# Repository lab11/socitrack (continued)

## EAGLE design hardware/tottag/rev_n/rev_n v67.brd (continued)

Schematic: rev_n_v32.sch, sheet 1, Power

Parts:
C7, C8: 22pF; 0201_CAP; MPN GRM0335C1H220FA01D
C9, C10: 470pF; 0402_CAP; MPN GRM1555C1H471JA01J; DIGIKEY 490-6242-1-ND
C15, C16: 10nF; 0402_CAP; MPN GRM155R71H103KA88J; DIGIKEY 490-6351-2-ND
C17, C18, C19: 22nF; 0402_CAP; MPN GRM155R71E223JA61D; DIGIKEY 490-10699-2-ND
C20, C21: 22nF; 0402_CAP; MPN CC0402ZRY5V8BB223; DIGIKEY 311-3823-1-ND
C27, C28, C29, C30: 0.1uF; 0402_CAP; MPN GRM155R71C104KA88J; DIGIKEY 490-6328-1-ND
C38, C39: 0.47uF; 0402_CAP; MPN GRT155R61E474ME01D; DIGIKEY 490-12270-1-ND
C40, C41, C42: 1uF; 0402_CAP; MPN GRM155R70J105KA12J
C45, C46, C47, C48: 4.7uF; 0603_CAP; MPN C1608X7S1A475K080AC
C53, C56, C57: 10uF; 0603_CAP; MPN CM105X5R106M25AT; DIGIKEY 1253-CM105X5R106M25ATCT-ND
J4: MOLEX-PICO-SPOX-3SIDE; MOLEX-PICO-SPOX-3_SIDE
JP2: JUMPER-SMT_3_1-NC_TRACE_SILK; SMT-JUMPER_3_1-NC_TRACE_SILK
JP9: PINHD-1X2; 1X02
JP10, JP11: PINHD-1X1; 1X01
L1, L2: 10uH; NRX3015; MPN NR3015T100M
L4: WURTH_COIL_760308103204
Q1: CSD75207W15; DSBGA
R6, R7: 97.6; 0402_RES; MPN RMCF0402FT97R6; DIGIKEY RMCF0402FT97R6CT-ND
R8, R9: 162; 0402_RES; MPN RMCF0402FT162R; DIGIKEY RMCF0402FT162RCT-ND
R13, R15: 2.2k; 0402_RES; MPN RC0402FR-072K2L
R18, R23: 10k; 0402_RES; MPN RC0402JR-0710KL; DIGIKEY 311-10KJRCT-ND
R26: 261k; 0201_RES; MPN ERJ-1GNF2613C
R27: 402k; 0201_RES; MPN ERJ-1GNF4023C
R28, R29: 845k; 0201_RES; MPN ERJ-1GNF8453C
R30: 1.87M; 0402_RES; TOLERANCE 1%; MPN RMCF0402FT1M87
R31: 5.1M; 0402_RES; TOLERANCE 1%; MPN RMCF0402FT5M10; DIGIKEY RMCF0402FT5M10CT-ND
R33, R34: 5.1M; 0402_RES; MPN RMCF0402FT5M10; DIGIKEY RMCF0402FT5M10CT-ND
RT1: 10k@25C; 0402_RES; MPN NCU15XH103F60RC; DIGIKEY 490-18149-1-ND
RX7, RX14: DNP; 0402_RES
S1: 450404015514; DIGIKEY 732-13665-1-ND
U3: BQ24040; DSQ0010A
U4: BQ51013B; RHL0020A
VR1: RT8020RT8020GQW; SON45P300X300X80-13T160X250N
XJ1: USB4110-GF-A; GCT_USB4110-GF-A
XR16, XR17: 5.1k; 0402_RES; MPN RMCF0402FT5K10; DIGIKEY RMCF0402FT5K10CT-ND
XR19: 10k; 0402_RES; MPN RC0402JR-0710KL; DIGIKEY 311-10KJRCT-ND

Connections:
!AD_EN: Q1.A1 (G1), Q1.C1 (G2), U4.8 (!AD-EN)
+2V5: C7.P$1 (1), C47.2, JP10.1, L1.P$2 (2), R28.2; also elsewhere on the board
AP4_GP18/TT_BATIN: C27.1, R30.2, R31.1; also elsewhere on the board
AP4_GP58/TT_!CHG: U3.8 (!CHG), U4.7 (!CHG); also elsewhere on the board
AP4_GP60/TT_!PG: U3.5 (!PG); also elsewhere on the board
AP4_GP66/TT_QI_TS_CTRL: C30.1, RT1.2, U4.13 (TS/CTRL); also elsewhere on the board
BATT_THERM: J4.2, J4.2SUPP (2), JP2.3; also elsewhere on the board
BATT_TS: JP2.2, U3.9 (TS); also elsewhere on the board
BQ_AC1: C9.1, C10.1, C15.2, C17.1, C18.1, C19.1, C20.2, C38.2, U4.2 (AC1)
BQ_AC2: C9.2, C10.2, C16.2, C21.2, C39.2, L4.P$2 (2), U4.19 (AC2)
BQ_BOOT1: C15.1, U4.3 (BOOT1)
BQ_BOOT2: C16.1, U4.17 (BOOT2)
BQ_CLAMP1: C38.1, U4.5 (CLAMP1)
BQ_CLAMP2: C39.1, U4.16 (CLAMP2)
BQ_COMM1: C20.1, U4.6 (COMM1)
BQ_COMM2: C21.1, U4.15 (COMM2)
BQ_FOD: R7.1, R9.2, R23.2, U4.14 (FOD)
BQ_ILM: R8.1, U4.12 (ILIM)
BQ_ISET: R15.2, U3.2 (ISET)
BQ_RECT: C28.1, C56.1, C57.1, R18.1, U4.18 (RECT)
COIL_AC1: C17.2, C18.2, C19.2, L4.P$1 (1)
D+: XJ1.A6 (DP1), XJ1.B6 (DP2)
D-: XJ1.A7 (DN1), XJ1.B7 (DN2)
GND: C27.2, C28.2, C29.2, C30.2, C40.1, C41.2, C42.2, C45.1, C46.2, C47.1, C48.2, C53.2, C56.2, C57.2, J4.1, J4.1SUPP (1), JP9.2, R6.2, R15.1, R26.1, R27.1, R30.1, RX7.1, RX14.1, U3.3 (VSS), U3.7 (ISET2), U3.PAD (VSS), U4.1 (PGND), U4.10 (EN1), U4.11 (EN2), U4.20 (PGND), U4.PAD (PGND), VR1.3 (GND2), VR1.9 (GND1), VR1.13 (GND2), XJ1.A1/B12 (GND), XJ1.B1/A12 (GND), XJ1.S1 (GND), XJ1.S2 (GND), XJ1.S3 (GND), XJ1.S4 (GND), XR16.2, XR17.2, XR19.1; also elsewhere on the board
unnamed: R6.1, R7.2
unnamed 122: JP2.1, XR19.2; also elsewhere on the board
unnamed: RX7.2, U3.4 (PRETERM)
unnamed: R18.2, R23.1
unnamed: R8.2, R9.1
unnamed: R13.2, RT1.1
unnamed 127: R13.1, RX14.2; also elsewhere on the board
VBAT: C42.1, J4.3, J4.3SUPP (3), JP9.1, S1.2, U3.10 (OUT); also elsewhere on the board
VBAT_SWITCHED: C45.2, C48.1, R31.2, R33.1, R34.1, S1.3, VR1.1 (VIN2), VR1.7 (VIN1)
VQI: C29.1, C41.1, C53.1, Q1.A2 (D1), Q1.A3 (D1), Q1.B3 (D1), U3.1 (IN), U4.4 (OUT)
VR1_1P8_EN: R34.2, VR1.6 (EN1)
VR1_2P5_EN: R33.2, VR1.12 (EN2)
VR1_FB1: C8.P$1 (1), R27.2, R29.2, VR1.4 (FB1)
VR1_FB2: C7.P$2 (2), R26.2, R28.1, VR1.10 (FB2)
VR1_LX1: L2.P$2 (2), VR1.8 (LX1)
VR1_LX2: L1.P$1 (1), VR1.2 (LX2)
VUSB: C40.2, Q1.B2 (D2), Q1.C2 (D2), Q1.C3 (D2), U4.9 (AD), XJ1.A4/B9 (VBUS), XJ1.B4/A9 (VBUS)

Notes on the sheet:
2.5V Rail DW.VDD2 88 mA (100) LNA 10.6 mA 9DOF 12.3 mA (15) Buzzer 90 mA (150) ------------------------ 200.9 mA (265) 40%I->L: 6.5 uH ( 9.2) ∆IL 85 mA (120) COUT=4.7uF, ESR@1.5MHz=0.005 ∆Vout 1.9 mV ( 2.7) ** After ^math, moved the VDDAUDA LDO from battery to hang off 2.5V for routing [plus some e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
1.8V Rail DW.VDD1 10 mA (10) DW.VDD3 70 mA (100) Flash 35 mA (50) 9DOF 12.3 mA (15) Apollo4 11.3 mA (120) ------------------------ 141.6 (295) 40%I->L: 5.8 uH ( 11.3) ∆IL 68 mA (132) COUT=4.7uF, ESR@1.5MHz=0.005 ∆Vout 1.5 mV ( 3)
Vout = Vref * (1 + R1/R2) Vref=0.6V, R1=850kΩ R2 = 850e3/((2.5/.6)-1) = 268.4kΩ R2 = 850e3/((1.875/.6)-1) = 400.0kΩ Note: 1.8 -> 1.875 to balance buffer above 1.8~1.85 for AP4 and below the hard max of 1.95 for the flash chip
Switch Current Rating: 250 mA (Assume 90% eff) 2.5: (150*2.5)/(3.4*.9) = 125 1.8: (200*1.8)/(3.4*.9) = 120
Actual: 402k -> 1.8687V
Actual: 261k -> 2.554V

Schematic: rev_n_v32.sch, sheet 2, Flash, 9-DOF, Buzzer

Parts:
C5, C6: 4pF; 0201_CAP; MPN GRM0335C1H4R0BA01D
C31, C32, C35, C36: 0.1uF; 0402_CAP; MPN CL05A104KP5NNNC
C44: 1uF; 0402_CAP; MPN GRM155R70J105KA12J
D4: DIODE0402; 0402_DIODE; MPN CDSQR400B-HF; DIGIKEY 641-2087-1-ND
LS1: PUI_SMT-0440-T-2-R; SMT-0440-T-2-R
Q2: MOSFET-NCHANNELXFDN-3; XFDFN-3
R12, R16, R20: 10k; 0402_RES; MPN RC0402JR-0710KL; DIGIKEY 311-10KJRCT-ND
R25: 100k; 0402_RES; MPN RT0402BRE07100KL
RX2, RX5, RX6, RX8, RX9: DNP; 0603-RES
RZ12: 0; 0402_RES; MPN RMCF0402ZT0R00
U6: BNO086; LGA28R0P510X4_5P2X3P8X1
U8: AS5FXXX04SND; AS5FXXXXXXXX-XXLXN
X2: TXC-9HT12; MPN 9HT12-32.768KDZY-T

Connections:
9DOF_CAP: C36.1, U6.9 (CAP)
9DOF_XI: C5.P$2 (2), U6.27 (XIN32), X2.2
9DOF_XO: C6.P$2 (2), U6.26 (XOUT32/CLKSEL1), X2.1
+2V5: C32.1, C44.1, D4.CATHODE, LS1.+, U6.3 (VDD); also elsewhere on the board
AP4_GP06/TT_FLASH_!HOLD_IO3: U8.7 (!HOLD!/SIO3); also elsewhere on the board
AP4_GP08/TT_9DOF_H_SCL/SCK/RX: RX6.2, U6.19 (H_SCL/SCK/RX); also elsewhere on the board
AP4_GP13/TT_9DOF_!BOOT: R20.1, U6.4 (!BOOT); also elsewhere on the board
AP4_GP17/TT_9DOF_H_!INT: U6.14 (H_INTN); also elsewhere on the board
AP4_GP30/TT_FLASH_!WP: U8.3 (!WP!/SIO2); also elsewhere on the board
AP4_GP47/TT_FLASH_SCK: U8.6 (SCLK); also elsewhere on the board
AP4_GP48/TT_FLASH_PDI_IO0: U8.5 (SI/SIO0); also elsewhere on the board
AP4_GP49/TT_FLASH_PDO_IO1: U8.2 (SO/SIO1); also elsewhere on the board
AP4_GP55/TT_BUZZER_GATE: Q2.G, R25.1; also elsewhere on the board
AP4_GP63/TT_9DOF_PS0/WAKE: U6.6 (PS0/WAKE); also elsewhere on the board
AP4_GP65/TT_9DOF_!RESET: RX8.1, U6.11 (!RESET); also elsewhere on the board
AP4_GP69/TT_FLASH_!CS: RX2.1, U8.1 (!CS); also elsewhere on the board
AP4_GP72/TT_9DOF_H_!CS: U6.18 (H_!CS); also elsewhere on the board
BNO_ENV_SCL: R12.1, U6.15 (ENV_SCL)
BNO_ENV_SDA: R16.1, U6.16 (ENV_SDA)
BNO_PS1: RX9.2, RZ12.1, U6.5 (PS1); also elsewhere on the board
GND: C5.P$1 (1), C6.P$1 (1), C31.2, C32.2, C35.2, C36.2, C44.2, Q2.S, R25.2, RX9.1, U6.2 (GND), U6.10 (CLKSEL0), U6.25 (GNDIO), U8.4 (GND); also elsewhere on the board
unnamed: D4.ANODE, LS1.- (N), Q2.D

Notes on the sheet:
Sup 1.7 - 1.98 V Qui 30 µA Max 30 mA
VDD 2.4 - 3.6 V, max 8 mA, qui 0.1 mA VDDIO 1.7 - 3.6 V, max 7 mA, qui 0.047 mA
Sup 2 - 4 V Nom 3 V Max 90 mA [50% DC]
If separate GNDIO ever relevant..
Datasheet— Does not give C int.. Digital pads typ 5pf, max 10pf CL = (C*C)/(C+C+) + Cstray C = 4 w/ only pads, as Cstray goes up, C rises, 4pF on should be okay
SEL0==GND -> XTAL
PS1 PS0 0 0 I2C 0 1 UART-RVC 1 0 UART 1 1 SPI

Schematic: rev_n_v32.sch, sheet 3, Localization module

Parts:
A1, A2, A3: ACR0301U
C2: 2pF; 0201_CAP; MPN CBR02C209A5GAC
C3, C4: 3.3pF; SMD_2012M-0805US-C; MPN 600F3R3BT250XT
C11: 0.1uF; SMD_3216M-1206US-C; MPN GRM31C5C1H104JA01L
C12, C13, C14: 4.7nF; SMD_1608M-0603US-C; MPN C0603C472J5GAC7867
C22, C24: 0.1uF; SMD_1608M-0603US-C; MPN C1608X7R1H104K080AA
C23, C25, C26, C33, C34: 0.1uF; 0402_CAP; MPN CL05A104KP5NNNC
C37: 0.22uF; SMD_1608M-0603US-C; MPN C1608X7R1H224K080AB
C43: 100pF; SMD_1005M-0402US-C; MPN C0402C101J3GACTU
C49, C50: 4.7uF; 0603_CAP; MPN C1608X7S1A475K080AC
C54, C55: 10uF; SMD_1608M-0603US-C; MPN CM105X5R106M25AT
C90, C91: 1uF; 0201_CAP; MPN GRM033R61A105ME44D
CX1, CX2: DNP; 0603_CAP
FB1: BLM03PG330SN1D; 0201_FB; MPN BLM03PG330SN1D
JP3, JP12: JUMPER-SMT_3_1-NC_TRACE_SILK; SMT-JUMPER_3_1-NC_TRACE_SILK
R1: 49.9-1%; 0201_RES; MPN ERJ-1GNF49R9C
R24: 100k; 0402_RES; MPN RT0402BRE07100KL
RX1: DNP; 0603-RES
RZ1, RZ2: 0; 0603-RES; MPN RMCF0603ZT0R00
RZ4: 0; 0402_RES; MPN RMCF0402ZT0R00
S2: SKY13373
S3: SIP3241XSIP32414; TDFN2X2X0P6-8
S4: MM8030-2610
TP0, TP1, TP2, TP3, TP4, TP5, TP6, TP7: TEST-POINT; PAD.03X.03
U2: DW3110; WLCSP52
U7: QM14068
VR3: TPS7A0218PDQNR; 4-XDFN-EP
X4: TXC-8Y; MPN 8Y38472012

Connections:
+2V5: C34.1, C49.1, C90.P$1 (1), RX1.1, S2.6 (VDD), S3.1 (IN), VR3.4 (IN); also elsewhere on the board
ANT1: A1.FEED, U7.2 (LNA_IN)
AP4_GP14/TT_!DW_SPI_CS: U2.B5 (!SPICS); also elsewhere on the board
AP4_GP24/TT_RFSW_V1: CX2.1, S2.4 (V1); also elsewhere on the board
AP4_GP25/TT_RFSW_V2: CX1.1, S2.5 (V2); also elsewhere on the board
AP4_GP26/TT_DW_WAKEUP: U2.B9 (WAKEUP); also elsewhere on the board
AP4_GP27/TT_DW_IRQ: R24.2, U2.B1 (IRQ/GPIO8); also elsewhere on the board
AP4_GP31/TT_DW_SPI_CLK: U2.A8 (SPICLK); also elsewhere on the board
AP4_GP32/TT_DW_SPI_IO0: U2.B7 (SPICDI(MOSI)); also elsewhere on the board
AP4_GP33/TT_DW_SPI_IO1: U2.A6 (SPICDO(MISO)); also elsewhere on the board
AP4_GP50/TT_!DW_RESET: U2.A10 (!RST); also elsewhere on the board
DW_EXTON: JP12.2, RX1.2, S3.2 (CTL), S3.3 (CTL), VR3.3 (EN); also elsewhere on the board
DW_EXTON_RAW: JP12.3, U2.A12 (EXTON); also elsewhere on the board
DW_GPIO4: TP4.P$1, U2.F1 (GPIO4/EXTPA)
DW_GPIO5: TP5.P$1, U2.D1 (GPIO5/EXTTXE/SPIPOL)
DW_GPIO6/EXTRXE: JP3.3, TP6.P$1, U2.C4 (GPIO6/EXTRXE/SPIPHA); also elsewhere on the board
DW_RF1: C2.P$1 (1), U2.H11 (RF1)
DW_RF2: R1.1, U2.H5 (RF2)
DW_RXLED: TP2.P$1, U2.E4 (GPIO2/RXLED)
DW_RXOKLED: TP0.P$1, U2.C2 (GPIO0/RXOKLED)
DW_SFDLED: TP1.P$1, U2.D3 (GPIO1/SFDLED)
DW_SYNC: TP7.P$1, U2.G2 (GPIO7/SYNC)
DW_TXLED: TP3.P$1, U2.E2 (GPIO3/TXLED)
DW_VDD2A: C12.P$1, FB1.P$2, U2.F15 (VDD2A)
DW_VDD2_PWROUT: C33.1, RZ1.1, S3.8 (OUT)
DW_VDD2_SUP: C13.P$1, C24.P$1, C55.P$1, FB1.P$1, RZ1.2, U2.B15 (VDD2B)
DW_VDD3_PWROUT: C25.1, RZ2.1, S3.5 (OUT)
DW_VDD3_SUP: C14.P$2, C22.P$2, C54.P$2, RZ2.2, U2.D15 (VDD3)
DW_VIO_D: C23.1, U2.A4 (VIO_D)
DW_VTX_D: C37.P$2, U2.C14 (VTX_D)
DW_XT0: C4.P$1, U2.G14 (XTO), X4.3 (2)
DW_XTI: C3.P$1, U2.H15 (XTI), X4.1
GND: C3.P$2, C4.P$2, C11.P$2, C12.P$2, C13.P$2, C14.P$1, C22.P$1, C23.2, C24.P$2, C25.2, C26.2, C33.2, C34.2, C37.P$1, C43.P$2, C49.2, C50.1, C54.P$1, C55.P$2, C90.P$2 (2), C91.P$2 (2), CX1.2, CX2.2, JP3.1, R1.2, R24.1, S2.2 (GND), S2.7 (GND), S2.8 (GND), S2.10 (GND), S2.12 (GND), S2.PAD (GND), S3.6 (GND), S3.7 (GND), S3.PAD (GND), S4.G1 (GND), S4.G2 (GND), U2.A2 (VSS), U2.A14 (VSS1), U2.B3 (VSS), U2.B11 (VSS1), U2.C6 (VSS), U2.C8 (VSS1), U2.C10 (VSS1), U2.C12 (VSS3), U2.D5 (VSS), U2.D7 (VSS), U2.D9 (VSS1), U2.D11 (VSS2), U2.D13 (VSS3), U2.E6 (GND-RF), U2.E10 (GND-RF), U2.E12 (GND-RF), U2.E14 (VSS2), U2.F7 (GND-RF), U2.F9 (GND-RF), U2.G6 (GND-RF), U2.G10 (GND-RF), U2.H1 (GND-RF), U2.H3 (GND-RF), U2.H7 (GND-RF), U2.H9 (GND-RF), U2.H13 (GND-RF), U7.3 (GND), U7.4 (GND), U7.5 (GND), U7.7 (GND), U7.9 (GND), VR3.2 (GND), VR3.PAD (GND), X4.2 (GND), X4.4 (GND); also elsewhere on the board
LNA_VCTRL: JP3.2, U7.8 (VCTRL); also elsewhere on the board
RF1: S2.9 (J2), U7.6 (LNA_OUT)
RF2: A2.FEED, S2.3 (J3)
RF3: A3.FEED, S2.1 (J1), S4.IN, S4.OUT (A)
RFC: C2.P$2 (2), S2.11 (RFC)
VDD_LNA: C11.P$1, C43.P$1, RZ4.2, U7.1 (VDD)
VR3_OUT: C91.P$1 (1), RZ4.1, VR3.1 (OUT)

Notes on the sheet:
Supply 2.4 - 3.6 V ds #'s @ 3.0 V min typ max VDD1 1.6 3.0 3.6 VDD2a,b 2.4 3.0 3.6 VDD3 1.5 3.0 3.6 Voltage on GPIO0-5, WAKEUP, RSTn, SPICSn, SPIMOSI, SPICLK -> Max: VDD1+0.3V I/O current (max): 10 mA VDD1 -> I/O Peak cont current is RX CH9: 88 mA TX worst-case: VDD2a/b: 20 mA VDD3: 20 mA RX worst-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
SupV 2.5-4.8 I/O V 1.65-min(3.3,SupV) Active: 60 µA Qui: 5 µA
V1 V2 State 0 0 Shutdown 1 0 RFC<>J2 0 1 RFC<>J1 1 1 RFC<>J3
Datasheet says no passives are needed However, EVB sch has 100 pF filters. Add hedge for option
Hedge: Allow disabling of low-power mode

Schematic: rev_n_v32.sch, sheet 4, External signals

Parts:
FD1, FD2, FD4, FD6: FIDUCIAL; FIDUCIAL_1MM-CU_2MM-MASK

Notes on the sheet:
Miscellany
Fiducials - Top
Fiducials - Bottom

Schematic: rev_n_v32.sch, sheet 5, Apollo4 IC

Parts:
A4: AMCA72-2R47G-S1F-T; AMCA72-2R470G-S1F-T
C1: 1.5pF; CAPC1005X60; TOLERANCE +/- 0.25pF; MPN C0402C159C5GACTU
C58, C59, C60, C61, C66, C67, C70, C71, C72, C73, C74, C75: 2.2uF; 0201_CAP; MPN GRM033R61A225KE47D
C62, C63, C64, C65, C79, C93: 1uF; 0201_CAP; MPN GRM033R61A105ME44D
C69: 4.7uF; 0402_CAP; MPN CL05A475MP5NRNC
C76: 4700pF; CAPC1005X60; MPN KGM05AR71E472KH
C80, C81: 6pF; CAPC1005X60; MPN GCM1555C1H6R0BA16D
CX3, CX4, CX5: DNP; CAPC1005X60
D3: ZENER; SODFL1608X70; MPN PESD5V0X1UB,135
L5: 2.2µH; 0805_CAP; MPN DFE201210U-2R2M=P2
L6: 1.0µH; 0603_CAP; MPN DFE18SAN1R0ME0L
L7: 2.0nH; INDC1006X60N; TOLERANCE +/- 0.1 nH; MPN LQG15HS2N0B02D
L8: 2.2nH; INDC1006X60N; TOLERANCE +/- 0.1 nH; MPN LQG15HN2N2B02D
RZ9: 0; 0402_RES; MPN RMCF0402ZT0R00
TP8: VDDBH; PAD.03X.03
TP9: VDDP; PAD.03X.03
TP10: VDDF; PAD.03X.03
U1: APOLLO4_BLUE_PLUS_SOC_KBR; APOLLO4_BLUE_SOC_BGA
X1: ABM12W; MPN ABM12W-32.0000MHZ-6-D1X-T3
X3: TXC-9HT12; MPN 9HT12-32.768KDZY-T

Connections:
AGND: C1.2, C93.P$2 (2), CX5.2, U1.M1 (RFIOM), U1.M3 (RFSUB-RF_SUBSTRATE_GND)
AP4_!RESET: C76.1, D3.1 (C), U1.A6 (!RST); also elsewhere on the board
AP4_GP06/TT_FLASH_!HOLD_IO3: U1.J5 (GPIO6); also elsewhere on the board
AP4_GP08/TT_9DOF_H_SCL/SCK/RX: U1.H2 (GPIO31); also elsewhere on the board
AP4_GP13/TT_9DOF_!BOOT: U1.D5 (GPIO13); also elsewhere on the board
AP4_GP14/TT_!DW_SPI_CS: U1.D6 (GPIO14); also elsewhere on the board
AP4_GP17/TT_9DOF_H_!INT: U1.D4 (GPIO17); also elsewhere on the board
AP4_GP18/TT_BATIN: U1.D3 (GPIO18); also elsewhere on the board
AP4_GP24/TT_RFSW_V1: U1.E2 (GPIO24); also elsewhere on the board
AP4_GP25/TT_RFSW_V2: U1.K5 (GPIO25); also elsewhere on the board
AP4_GP26/TT_DW_WAKEUP: U1.L5 (GPIO26); also elsewhere on the board
AP4_GP27/TT_DW_IRQ: U1.M5 (GPIO27); also elsewhere on the board
AP4_GP30/TT_FLASH_!WP: U1.G4 (GPIO30); also elsewhere on the board
AP4_GP31/TT_DW_SPI_CLK: U1.E8 (GPIO8); also elsewhere on the board
AP4_GP32/TT_DW_SPI_IO0: U1.E7 (GPIO9); also elsewhere on the board
AP4_GP33/TT_DW_SPI_IO1: U1.E6 (GPIO10); also elsewhere on the board
AP4_GP47/TT_FLASH_SCK: U1.F1 (GPIO47); also elsewhere on the board
AP4_GP48/TT_FLASH_PDI_IO0: U1.E1 (GPIO48); also elsewhere on the board
AP4_GP49/TT_FLASH_PDO_IO1: U1.D1 (GPIO49); also elsewhere on the board
AP4_GP50/TT_!DW_RESET: U1.A9 (GPIO50); also elsewhere on the board
AP4_GP51/LED1_GREEN: U1.B9 (GPIO51); also elsewhere on the board
AP4_GP53/LED1_RED: U1.C9 (GPIO53); also elsewhere on the board
AP4_GP55/TT_BUZZER_GATE: U1.D9 (GPIO55); also elsewhere on the board
AP4_GP58/TT_!CHG: U1.J7 (GPIO58); also elsewhere on the board
AP4_GP60/TT_!PG: U1.K8 (GPIO60); also elsewhere on the board
AP4_GP63/TT_9DOF_PS0/WAKE: U1.M6 (GPIO63); also elsewhere on the board
AP4_GP65/TT_9DOF_!RESET: U1.A7 (GPIO65); also elsewhere on the board
AP4_GP66/TT_QI_TS_CTRL: U1.A8 (GPIO66); also elsewhere on the board
AP4_GP69/TT_FLASH_!CS: U1.B8 (GPIO69); also elsewhere on the board
AP4_GP72/TT_9DOF_H_!CS: U1.C8 (GPIO72); also elsewhere on the board
AP4_GP79/LED2_RED: U1.M11 (GPIO79); also elsewhere on the board
AP4_GP88/LED2_YLW: U1.F9 (GPIO88); also elsewhere on the board
AP4_LPADC_VREF: C79.P$2 (2), U1.A12 (LPADC_VREF)
AP4_LPMICBIAS: C71.P$2 (2), U1.B10 (LPMICBIAS)
AP4_RFIOP1: CX5.1, L7.1, U1.M2 (RFIOP)
AP4_SWDCLK: U1.K3 (GPIO20); also elsewhere on the board
AP4_SWDIO: U1.J3 (GPIO21); also elsewhere on the board
AP4_SWO: U1.L4 (GPIO3); also elsewhere on the board
AP4_USB0_N: U1.M8 (USB0PN)
AP4_USB0_P: U1.M7 (USB0PP)
AP4_VDDBH: C69.1, L6.2, RZ9.1, TP8.P$1, U1.G12 (VDDBH--BLE_BUCK_VOUT)
AP4_VDDBH_RF: C93.P$1 (1), RZ9.2, U1.J1 (VDDBH_RF--BLE_BUCK_RF_VOUT)
AP4_VDDBH_SW: L6.1, U1.H12 (VDDBH_SW--BLE_BUCK_SW)
AP4_VDDC: C59.P$1 (1), U1.A3 (VDDC-CORE)
AP4_VDDC_LV: C60.P$1 (1), U1.B3 (VDDC_LV-CORE_LV)
AP4_VDDF: C61.P$1 (1), C75.P$1 (1), TP10.P$1, U1.C2 (VDDF-MEM)
AP4_VDDMIPI_1P8: C70.P$1 (1), U1.H10 (VDD18-MIPI); also elsewhere on the board
AP4_VDDS: C58.P$1 (1), U1.C1 (VDDS-SRAM_HV_SUP)
AP4_VDDUSB_0P9: C73.P$1 (1), U1.L7 (VDDUSB0P9); also elsewhere on the board
AP4_VDDUSB_3P3: C74.P$1 (1), U1.K7 (VDDUSB33); also elsewhere on the board
AP4_XI: C81.1, U1.A4 (XI), X3.2
AP4_XI32M: CX4.1, U1.C12 (XI32M), X1.3 (2)
AP4_XO: C80.1, U1.A5 (XO), X3.1
AP4_XO32M: CX3.1, U1.D12 (XO32M), X1.1
BLE_RFOUT: A4.S1, L8.2
GND: C58.P$2 (2), C59.P$2 (2), C60.P$2 (2), C61.P$2 (2), C62.P$2 (2), C63.P$2 (2), C64.P$2 (2), C65.P$2 (2), C66.P$2 (2), C67.P$2 (2), C69.2, C70.P$2 (2), C71.P$1 (1), C72.P$2 (2), C73.P$2 (2), C74.P$2 (2), C76.2, C79.P$1 (1), C80.2, C81.2, CX3.2, CX4.2, D3.2 (A), U1.B2 (VSSP-BUCK_REGS_GND), U1.B5 (VSSA-ANALOG_GND), U1.B12 (VSSAUDA), U1.D2 (VSS-DGND_FOR_VDDF_AND_PADS), U1.E12 (VSSAUDD), U1.H1 (VSSB-BLE_UNREG_GND), U1.J10 (VSS18-MIPI), U1.L1 (VSSVCO-BLECORE_GND_FOR_VCO), U1.L2 (VSSS-HVSIMOBUCK_GND), U1.L8 (VSSAUSB), X1.2 (GND), X1.4 (GND); also elsewhere on the board
unnamed: C1.1, L7.2, L8.1
SIMOBUCK_SW: L5.P$1 (1), U1.A1 (SIMOBUCK_SW)
SIMOBUCK_SWSEL: L5.P$2 (2), U1.A2 (SIMOBUCK_SWSEL)
VDDAUDA_1P8-CLEAN: C72.P$1 (1), U1.B11 (VDDAUDA); also elsewhere on the board

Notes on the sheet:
Supply 1.8-2.0 V M4 max sust: 4 mA Buck spikes: 100 mA BLE max sus: 6 mA (+1.2?) BLE buck spk: 2.2 mA
Note: Load caps DNP on Ambiq reference assembly
Int PUs, safe float
If Unused: Float data; gnd usb pwr
If Unused (no display): Float clk,data; gnd pwr
Unused (no mic yet..) Float inputs and bias out VRef always gen'd internally and expects 100nF cap
No idea what this does :( Datasheet doesn't explain anywhere. Reference board just pins out to general header
I/O Planning Notes
3 MSPI instances - MSPI0 seems normal, use → GPIO64-73 (PadFn0) - MSPI1-2 have many caveats, avoid
7 IOM (I2C/SPI), two power domains - IOM0-3 HCPB - IOM5-7 HCPC IOMn_SUBMODCTRL_SMODnEN reg disables submodule
MSPI0
IOM0
IOM1
Timers (PWM/buzzer) any GPIO pin (Pad Fn6)
KBR Package
For the KBR package of the Apollo4 Blue Plus SoC, the pins available for chip enables for the MSPI instances are limited to: GPIO14, 52, 56, 57, 60, 73, 75, 83, 84, 85, 86 and 91.
§30.2.4-6 Recommended Buck,Bypass,Ext Components
SWD Pins (req)
VREF generated internally, ext cap is filter
IOM3
AP4 datasheet— XI/XO int C: 3.4pF max ext C: 7 pF
AP4 datasheet— XI/XO int C: 3.4pF C-load: 6 pF (max) ESR: 100 Ω
Pad Fn4
Pad Fn2
Pad Fn0
Note: Load caps DNP after first-gen fab testing. EVB Populates with 6pF
Route USB0PN and USB0PP as 90Ω differential pair
Route CLKN, CLKP as 100Ω diff pair and 50Ω single-ended trcs
Route D0N and D0P as 100Ω diff pair and 50Ω signle-ended trcs
NOTE: EVB and ref sch have a 0.1uF here. As this is unused, replaced with 1uF to reduce BOM count.
IOM2
IOM5
IOM6
IOM7

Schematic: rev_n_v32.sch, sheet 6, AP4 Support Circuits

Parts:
C77, C78: 1uF; 0201_CAP; MPN GRM033R61A105ME44D
D1: BICOLOR-SMD; LED-0606; MPN MCL0606FRD1GR1T
D2: BICOLOR-SMD; LED-0606; MPN MCL0606FYW1RD1T
J1, J2: TC2030-JLINK-NL-2SIDE; TC2030-IDC-NL-2SIDE
JP1: JUMPER-SMT_2_NC_TRACE_SILK; SMT-JUMPER_2_NC_TRACE_SILK
R2, R3: 5.1; 0402_RES; MPN RC0402JR-075R1L
R4, R5: 15; 0402_RES; MPN RC0402JR-0715RL
RZ6, RZ7, RZ8, RZ10, RZ11: 0; 0402_RES; MPN RMCF0402ZT0R00
VR2: TPS7A0218PDQNR; 4-XDFN-EP

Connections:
+2V5: C77.P$1 (1), RZ10.1, VR2.4 (IN); also elsewhere on the board
AP4_!RESET: J1.3 (!RESET), J1.B3 (!RESET); also elsewhere on the board
AP4_GP51/LED1_GREEN: R2.2; also elsewhere on the board
AP4_GP53/LED1_RED: R5.2; also elsewhere on the board
AP4_GP79/LED2_RED: R4.2; also elsewhere on the board
AP4_GP88/LED2_YLW: R3.2; also elsewhere on the board
AP4_LED2_BLUE_COMM: D1.C1, R5.1
AP4_LED_BLUE_COMM: D2.C2, R3.1
AP4_LED_GREEN_COMM: D2.C1, R4.1
AP4_LED_RED_COMM: D1.C2, R2.1
AP4_SWDCLK: J1.4 (SWDCLK), J1.B4 (SWDCLK); also elsewhere on the board
AP4_SWDIO: J1.2 (SWDIO), J1.B2 (SWDIO); also elsewhere on the board
AP4_SWO: J1.6 (SWO), J1.B6 (SWO); also elsewhere on the board
AP4_VDDMIPI_1P8: RZ8.1; also elsewhere on the board
AP4_VDDUSB_0P9: RZ6.1; also elsewhere on the board
AP4_VDDUSB_3P3: RZ7.1; also elsewhere on the board
GND: C77.P$2 (2), C78.P$2 (2), J1.5 (GND), J1.B5 (GND), J2.5 (GND), J2.B5 (GND), RZ6.2, RZ7.2, RZ8.2, VR2.2 (GND), VR2.PAD (GND); also elsewhere on the board
LED_SUP: D1.A1, D1.A2, D2.A1, D2.A2, JP1.1; also elsewhere on the board
VDDAUDA_1P8-CLEAN: RZ11.2; also elsewhere on the board
VR2_EN: RZ10.2, VR2.3 (EN)
VR2_OUT: C78.P$1 (1), RZ11.1, VR2.1 (OUT)

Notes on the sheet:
Ambiq Eng Note— VDDAUDA must be powered (even if not using BLE or AUDADC). I see you have an enable triggered by a pin. Note this can cause issues.
datasheet est's Rdrp =Ω If tgt: 20 mA ~~cheap 0402 R's dissp limit 10mW~~ 1.8 SUPPLY 2.5 SUPPLY Vf red: 1.5 0.3V 15Ω 6mW 1.0V 50Ω 20mW Vf grn: 1.7 0.1V 5Ω 2mW 0.8V 40Ω 16mW Vf blu: 1.7 0.1V 5Ω 2mW 0.8V 40Ω 16mW

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
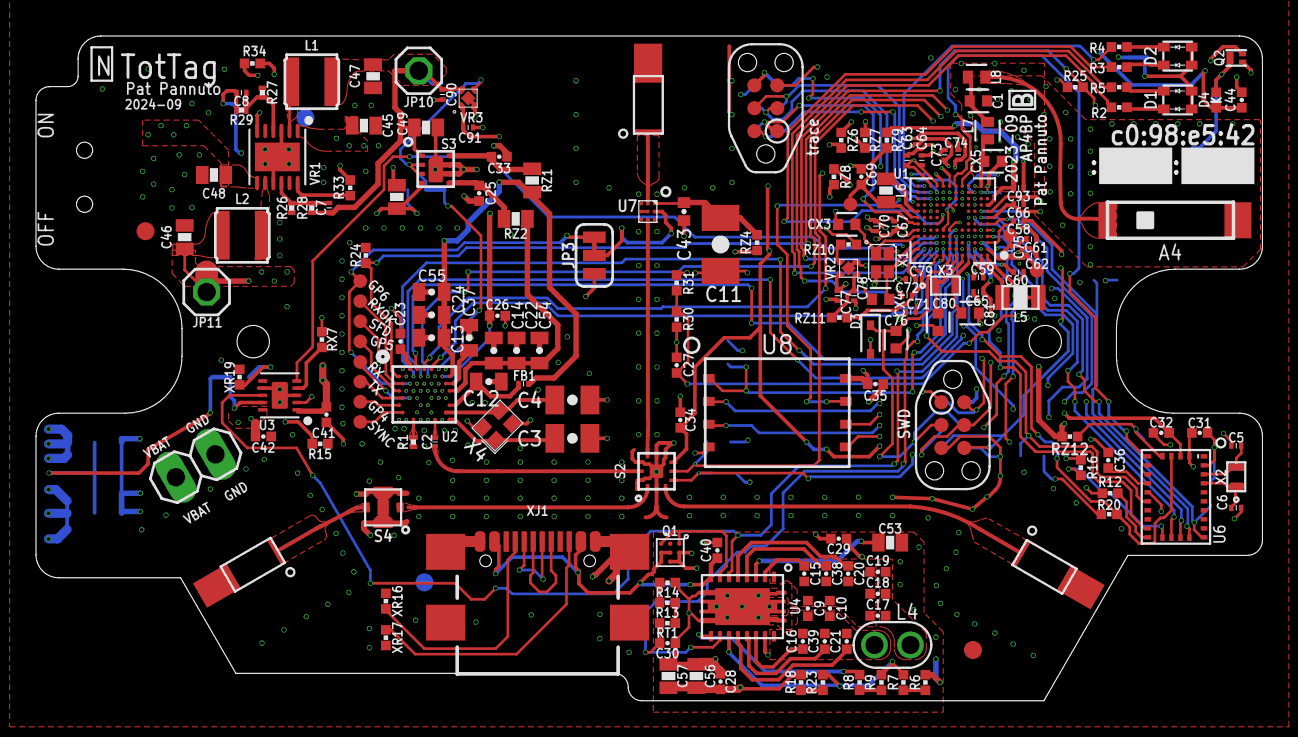
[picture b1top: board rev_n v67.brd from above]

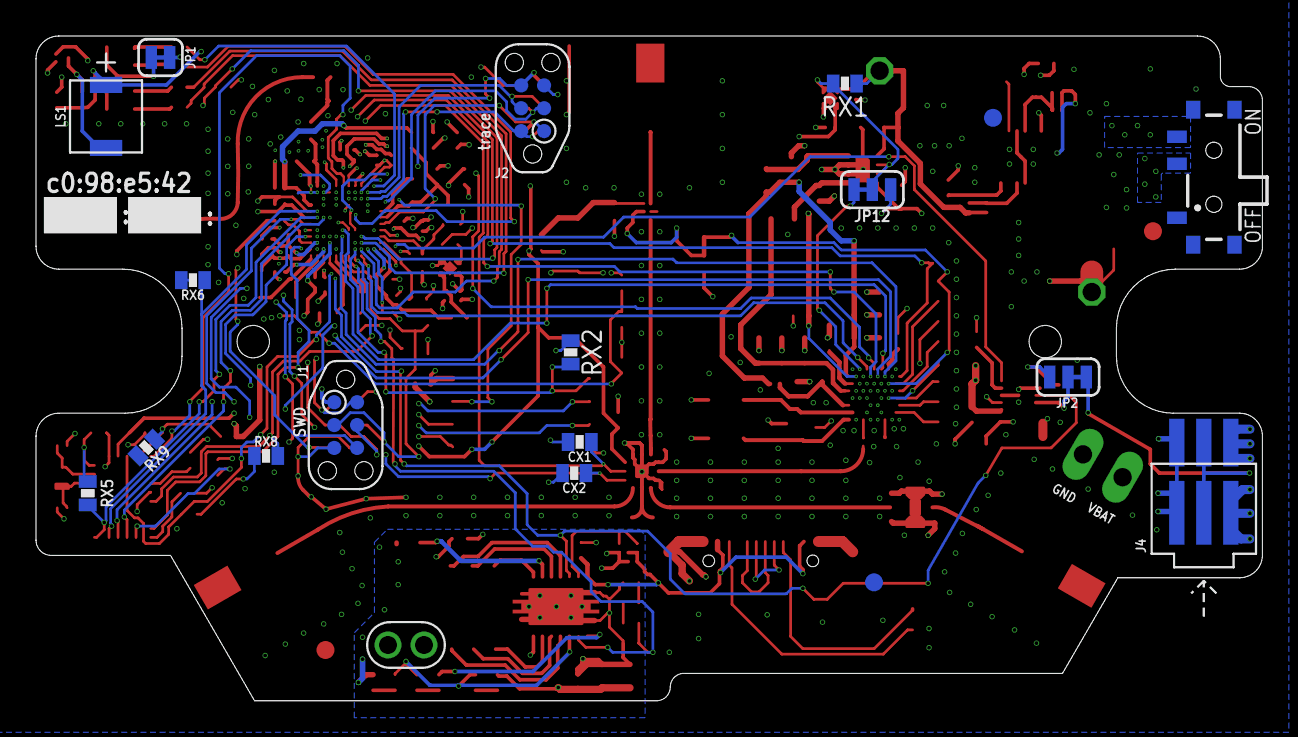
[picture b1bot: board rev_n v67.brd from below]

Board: 4 copper layers, 68.1 x 36.9 mm, 197 parts (16 on the bottom side), 147 nets.

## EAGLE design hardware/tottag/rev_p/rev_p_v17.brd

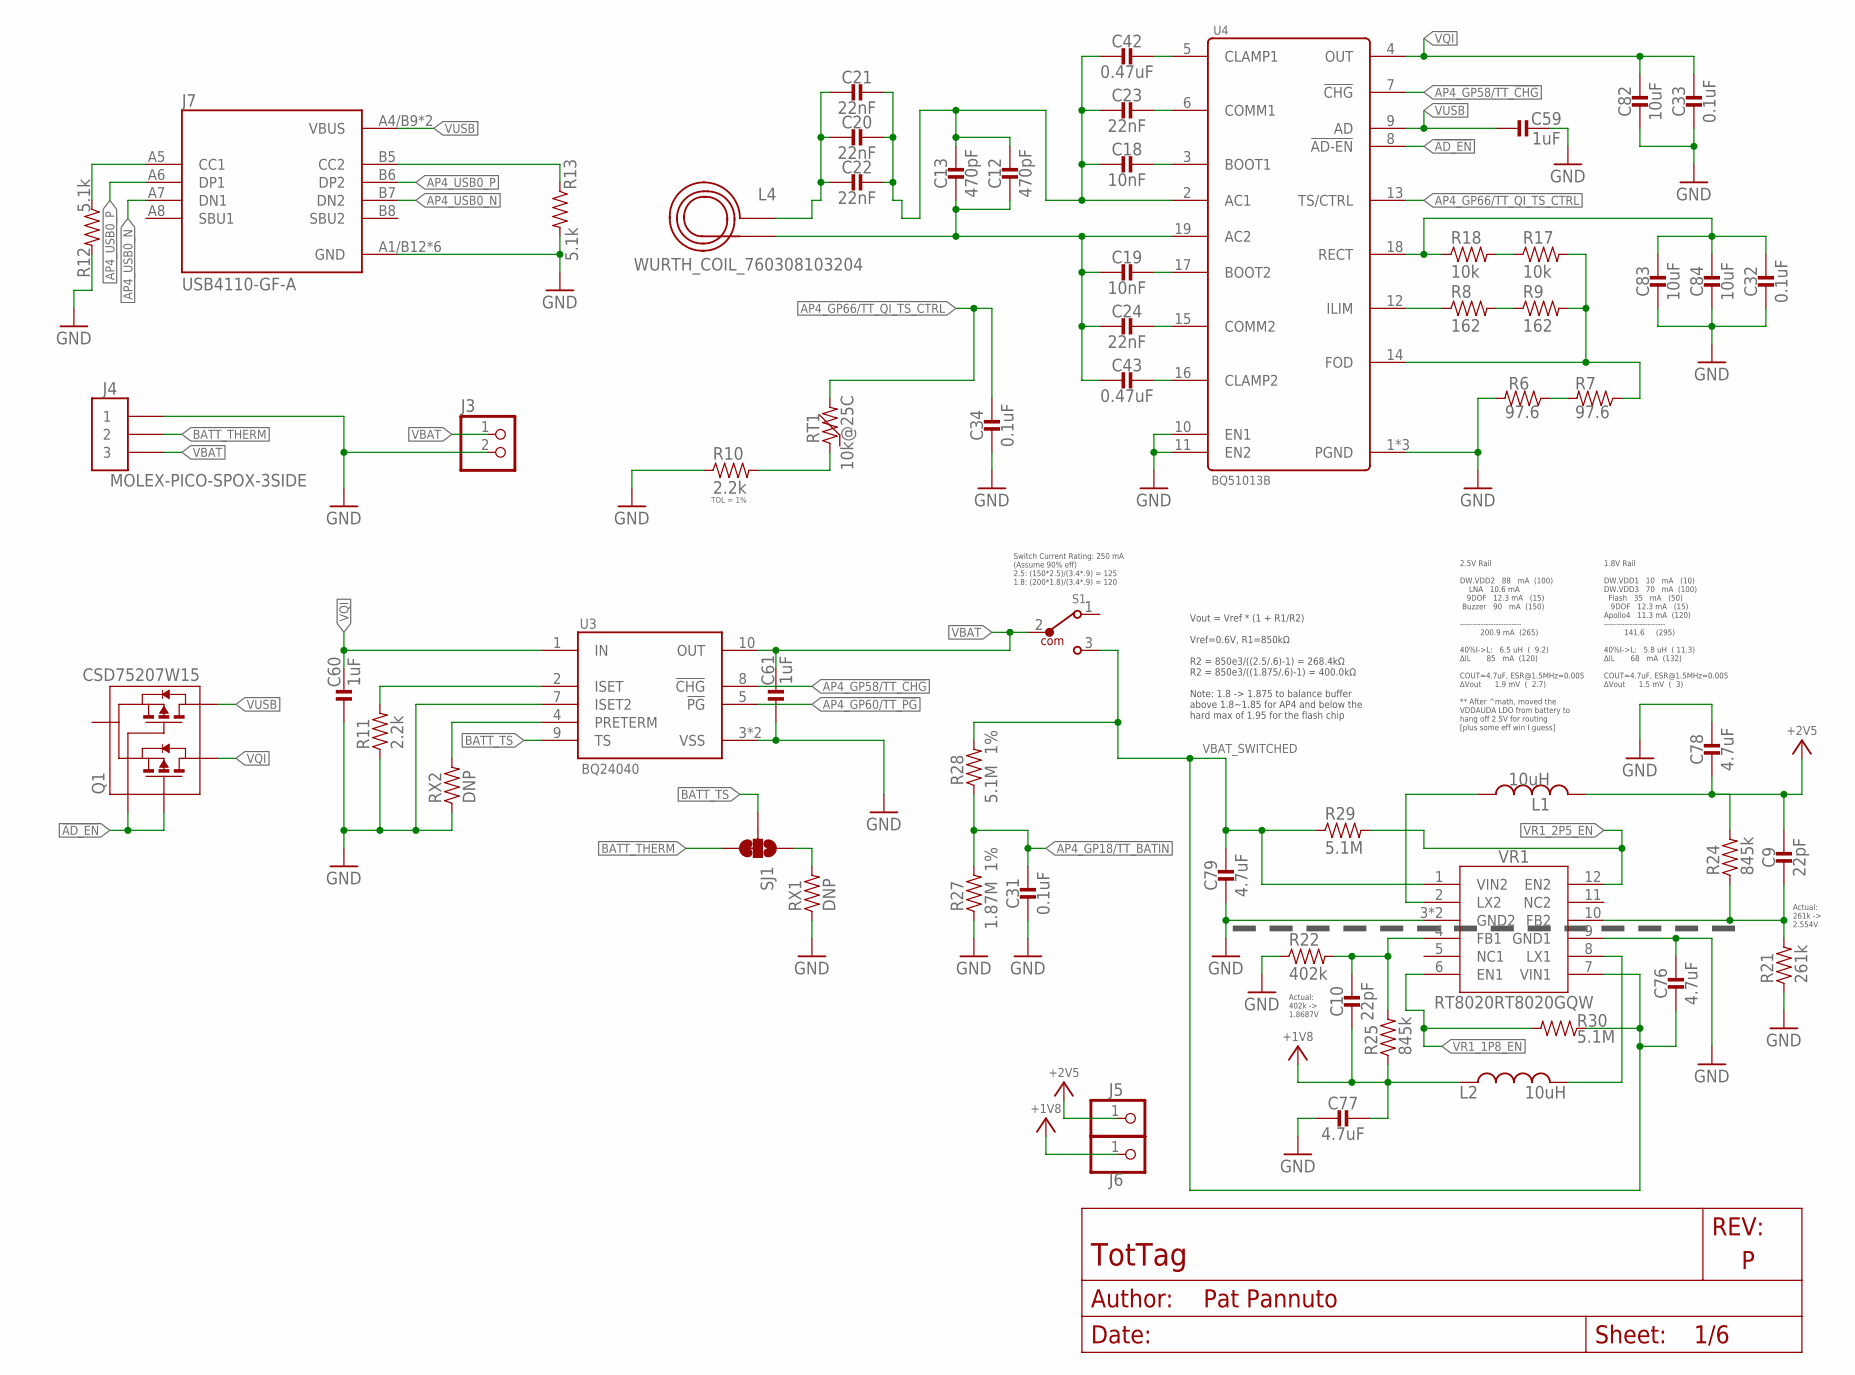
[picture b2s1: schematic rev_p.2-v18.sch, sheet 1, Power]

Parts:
C9, C10: 22pF; 0201_CAP; MPN GRM0335C1H220FA01D
C12, C13: 470pF; 0402_CAP; MPN GRM1555C1H471JA01J; DIGIKEY 490-6242-1-ND
C18, C19: 10nF; 0402_CAP; MPN GRM155R71H103KA88J; DIGIKEY 490-6351-2-ND
C20, C21, C22: 22nF; 0402_CAP; MPN GRM155R71E223JA61D; DIGIKEY 490-10699-2-ND
C23, C24: 22nF; 0402_CAP; MPN CC0402ZRY5V8BB223; DIGIKEY 311-3823-1-ND
C31, C32, C33, C34: 0.1uF; 0402_CAP; MPN GRM155R71C104KA88J; DIGIKEY 490-6328-1-ND
C42, C43: 0.47uF; 0402_CAP; MPN C1005X5R1E474K050BB
C59, C60, C61: 1uF; 0201_CAP; MPN GRM033R61A105ME44D
C76, C77, C78, C79: 4.7uF; 0603_CAP; MPN C1608X7S1A475K080AC
C82, C83, C84: 10uF; 0603_CAP; MPN CM105X5R106M25AT; DIGIKEY 1253-CM105X5R106M25ATCT-ND
J3: PINHD-1X2; 1X02
J4: MOLEX-PICO-SPOX-3SIDE; MOLEX-PICO-SPOX-3_SIDE
J5, J6: PINHD-1X1; 1X01
J7: USB4110-GF-A; GCT_USB4110-GF-A
L1, L2: 10uH; NRX3015; MPN NR3015T100M
L4: WURTH_COIL_760308103204
Q1: CSD75207W15; DSBGA
R6, R7: 97.6; 0402_RES; MPN RMCF0402FT97R6; DIGIKEY RMCF0402FT97R6CT-ND
R8, R9: 162; 0402_RES; MPN RMCF0402FT162R; DIGIKEY RMCF0402FT162RCT-ND
R10, R11: 2.2k; 0402_RES; MPN RC0402FR-072K2L
R12, R13: 5.1k; 0402_RES; MPN RMCF0402FT5K10; DIGIKEY RMCF0402FT5K10CT-ND
R17, R18: 10k; 0402_RES; MPN RC0402JR-0710KL; DIGIKEY 311-10KJRCT-ND
R21: 261k; 0201_RES; MPN ERJ-1GNF2613C
R22: 402k; 0201_RES; MPN ERJ-1GNF4023C
R24, R25: 845k; 0201_RES; MPN ERJ-1GNF8453C
R27: 1.87M; 0402_RES; TOLERANCE 1%; MPN RMCF0402FT1M87
R28: 5.1M; 0402_RES; TOLERANCE 1%; MPN RMCF0402FT5M10; DIGIKEY RMCF0402FT5M10CT-ND
R29, R30: 5.1M; 0402_RES; MPN RMCF0402FT5M10; DIGIKEY RMCF0402FT5M10CT-ND
RT1: 10k@25C; 0402_RES; MPN NCU15XH103F60RC; DIGIKEY 490-18149-1-ND
RX1, RX2: DNP; 0402_RES
S1: 450404015514; DIGIKEY 732-13665-1-ND
SJ1: JUMPER-SMT_3_1-NC_TRACE_SILK; SMT-JUMPER_3_1-NC_TRACE_SILK
U3: BQ24040; DSQ0010A
U4: BQ51013B; RHL0020A
VR1: RT8020RT8020GQW; SON45P300X300X80-13T160X250N

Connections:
!AD_EN: Q1.A1 (G1), Q1.C1 (G2), U4.8 (!AD-EN)
+1V8: C10.P$2 (2), C77.1, J6.1, L2.P$1 (1), R25.1; also elsewhere on the board
+2V5: C9.P$1 (1), C78.2, J5.1, L1.P$2 (2), R24.2; also elsewhere on the board
AP4_GP18/TT_BATIN: C31.1, R27.2, R28.1; also elsewhere on the board
AP4_GP58/TT_!CHG: U3.8 (!CHG), U4.7 (!CHG); also elsewhere on the board
AP4_GP60/TT_!PG: U3.5 (!PG); also elsewhere on the board
AP4_GP66/TT_QI_TS_CTRL: C34.1, RT1.2, U4.13 (TS/CTRL); also elsewhere on the board
AP4_USB0_N: J7.A7 (DN1), J7.B7 (DN2); also elsewhere on the board
AP4_USB0_P: J7.A6 (DP1), J7.B6 (DP2); also elsewhere on the board
BATT_THERM: J4.2, J4.2SUPP (2), SJ1.3
BATT_TS: SJ1.2, U3.9 (TS)
BQ_AC1: C12.1, C13.1, C18.2, C20.1, C21.1, C22.1, C23.2, C42.2, U4.2 (AC1)
BQ_AC2: C12.2, C13.2, C19.2, C24.2, C43.2, L4.P$2 (2), U4.19 (AC2)
BQ_BOOT1: C18.1, U4.3 (BOOT1)
BQ_BOOT2: C19.1, U4.17 (BOOT2)
BQ_CLAMP1: C42.1, U4.5 (CLAMP1)
BQ_CLAMP2: C43.1, U4.16 (CLAMP2)
BQ_COMM1: C23.1, U4.6 (COMM1)
BQ_COMM2: C24.1, U4.15 (COMM2)
BQ_FOD: R7.1, R9.2, R17.2, U4.14 (FOD)
BQ_ILM: R8.1, U4.12 (ILIM)
BQ_ISET: R11.2, U3.2 (ISET)
BQ_RECT: C32.1, C83.1, C84.1, R18.1, U4.18 (RECT)
COIL_AC1: C20.2, C21.2, C22.2, L4.P$1 (1)
GND: C31.2, C32.2, C33.2, C34.2, C59.P$2 (2), C60.P$1 (1), C61.P$1 (1), C76.1, C77.2, C78.1, C79.2, C82.2, C83.2, C84.2, J3.2, J4.1, J4.1SUPP (1), J7.A1/B12 (GND), J7.B1/A12 (GND), J7.S1 (GND), J7.S2 (GND), J7.S3 (GND), J7.S4 (GND), R6.2, R10.1, R11.1, R12.2, R13.2, R21.1, R22.1, R27.1, RX1.1, RX2.1, U3.3 (VSS), U3.7 (ISET2), U3.PAD (VSS), U4.1 (PGND), U4.10 (EN1), U4.11 (EN2), U4.20 (PGND), U4.PAD (PGND), VR1.3 (GND2), VR1.9 (GND1), VR1.13 (GND2); also elsewhere on the board
unnamed: R6.1, R7.2
unnamed: RX1.2, SJ1.1
unnamed: RX2.2, U3.4 (PRETERM)
unnamed: R17.1, R18.2
unnamed: R8.2, R9.1
unnamed: R10.2, RT1.1
USB_CC1: J7.A5 (CC1), R12.1
USB_CC2: J7.B5 (CC2), R13.1
VBAT: C61.P$2 (2), J3.1, J4.3, J4.3SUPP (3), S1.2, U3.10 (OUT)
VBAT_SWITCHED: C76.2, C79.1, R28.2, R29.1, R30.1, S1.3, VR1.1 (VIN2), VR1.7 (VIN1); also elsewhere on the board
VQI: C33.1, C60.P$2 (2), C82.1, Q1.A2 (D1), Q1.A3 (D1), Q1.B3 (D1), U3.1 (IN), U4.4 (OUT)
VR1_1P8_EN: R30.2, VR1.6 (EN1)
VR1_2P5_EN: R29.2, VR1.12 (EN2)
VR1_FB1: C10.P$1 (1), R22.2, R25.2, VR1.4 (FB1)
VR1_FB2: C9.P$2 (2), R21.2, R24.1, VR1.10 (FB2)
VR1_LX1: L2.P$2 (2), VR1.8 (LX1)
VR1_LX2: L1.P$1 (1), VR1.2 (LX2)
VUSB: C59.P$1 (1), J7.A4/B9 (VBUS), J7.B4/A9 (VBUS), Q1.B2 (D2), Q1.C2 (D2), Q1.C3 (D2), U4.9 (AD); also elsewhere on the board

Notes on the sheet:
2.5V Rail DW.VDD2 88 mA (100) LNA 10.6 mA 9DOF 12.3 mA (15) Buzzer 90 mA (150) ------------------------ 200.9 mA (265) 40%I->L: 6.5 uH ( 9.2) ∆IL 85 mA (120) COUT=4.7uF, ESR@1.5MHz=0.005 ∆Vout 1.9 mV ( 2.7) ** After ^math, moved the VDDAUDA LDO from battery to hang off 2.5V for routing [plus some e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
1.8V Rail DW.VDD1 10 mA (10) DW.VDD3 70 mA (100) Flash 35 mA (50) 9DOF 12.3 mA (15) Apollo4 11.3 mA (120) ------------------------ 141.6 (295) 40%I->L: 5.8 uH ( 11.3) ∆IL 68 mA (132) COUT=4.7uF, ESR@1.5MHz=0.005 ∆Vout 1.5 mV ( 3)
Vout = Vref * (1 + R1/R2) Vref=0.6V, R1=850kΩ R2 = 850e3/((2.5/.6)-1) = 268.4kΩ R2 = 850e3/((1.875/.6)-1) = 400.0kΩ Note: 1.8 -> 1.875 to balance buffer above 1.8~1.85 for AP4 and below the hard max of 1.95 for the flash chip
Switch Current Rating: 250 mA (Assume 90% eff) 2.5: (150*2.5)/(3.4*.9) = 125 1.8: (200*1.8)/(3.4*.9) = 120
Actual: 402k -> 1.8687V
Actual: 261k -> 2.554V
